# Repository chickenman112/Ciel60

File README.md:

# Ciel60
Resources for Ciel60

I am not responsible if these files do not work

HS pcb uses RMI's footprints

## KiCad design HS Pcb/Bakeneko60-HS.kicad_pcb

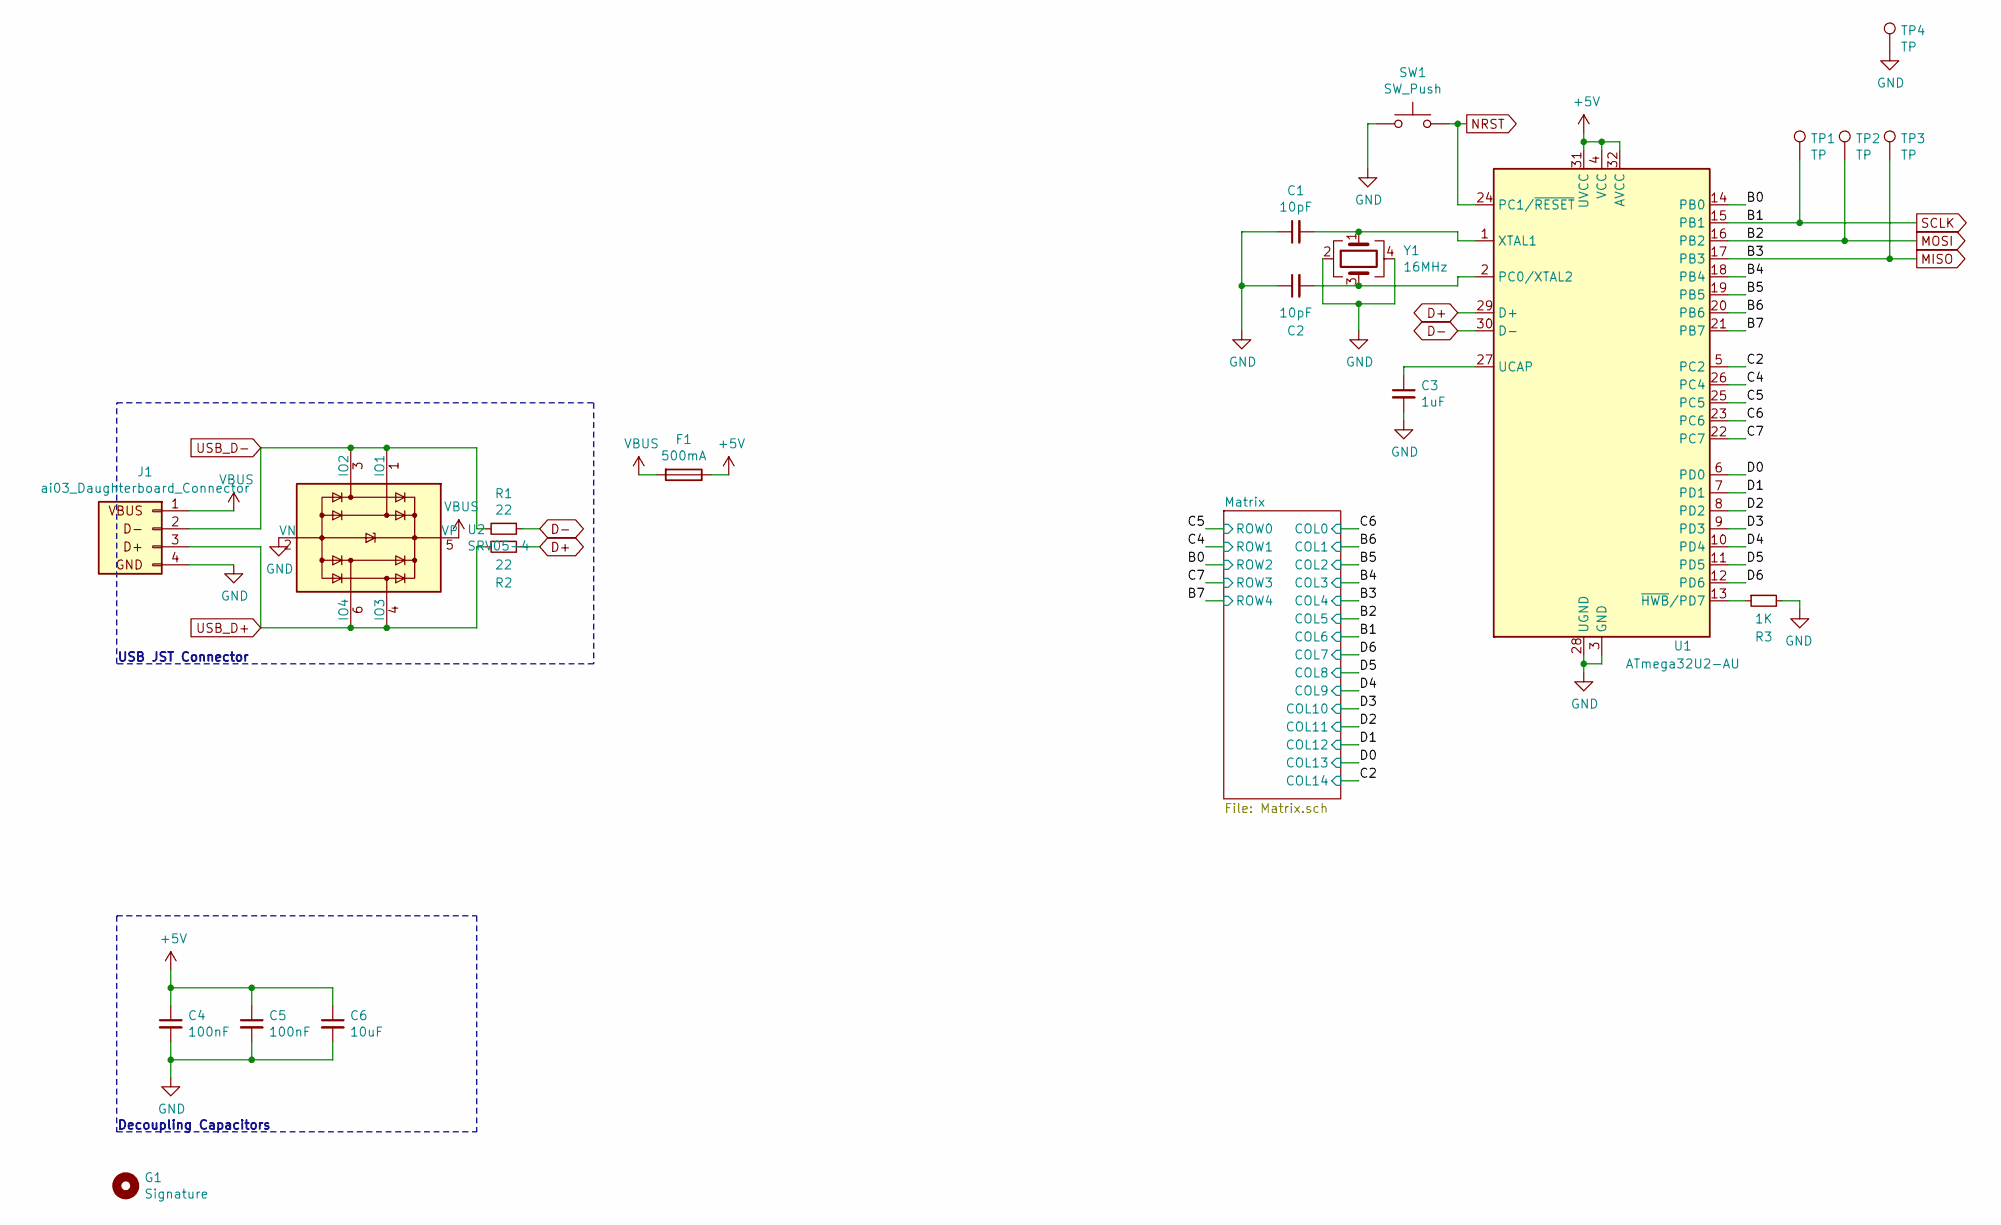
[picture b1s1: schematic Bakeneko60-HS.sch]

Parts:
C1, C2: 10pF; C_0603_1608Metric
C3: 1uF; C_0603_1608Metric
C4, C5: 100nF; C_0603_1608Metric
C6: 10uF; C_0805_2012Metric
F1: 500mA; Fuse_1206_3216Metric
G1: Signature
J1: ai03_Daughterboard_Connector; JST_SH_SM04B-SRSS-TB_1x04-1MP_P1.00mm_Horizontal
R1, R2: 22; R_0603_1608Metric
R3: 1K; R_0603_1608Metric
SW1: SW_Push; SW_SPST_TL3342
TP1, TP2, TP3, TP4: TP; TestPoint_Pad_D1.0mm
U1: ATmega32U2-AU; TQFP-32_7x7mm_P0.8mm
U2: SRV05-4; SOT-23-6
Y1: 16MHz; Crystal_SMD_3225-4Pin_3.2x2.5mm

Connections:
+5V: C4.1, C5.1, C6.1, F1.1, U1.4 (VCC), U1.31 (UVCC), U1.32 (AVCC)
/B0: U1.14 (PB0); also elsewhere on the board
/B4: U1.18 (PB4); also elsewhere on the board
/B5: U1.19 (PB5); also elsewhere on the board
/B6: U1.20 (PB6); also elsewhere on the board
/B7: U1.21 (PB7); also elsewhere on the board
/C2: U1.5 (PC2); also elsewhere on the board
/C4: U1.26 (PC4); also elsewhere on the board
/C5: U1.25 (PC5); also elsewhere on the board
/C6: U1.23 (PC6); also elsewhere on the board
/C7: U1.22 (PC7); also elsewhere on the board
/D0: U1.6 (PD0); also elsewhere on the board
/D1: U1.7 (PD1); also elsewhere on the board
/D2: U1.8 (PD2); also elsewhere on the board
/D3: U1.9 (PD3); also elsewhere on the board
/D4: U1.10 (PD4); also elsewhere on the board
/D5: U1.11 (PD5); also elsewhere on the board
/D6: U1.12 (PD6); also elsewhere on the board
D+: R2.2, U1.29 (D+)
D-: R1.1, U1.30 (D-)
GND: C1.1, C2.1, C3.2, C4.2, C5.2, C6.2, J1.4 (GND), R3.2, SW1.1, TP4.1, U1.3 (GND), U1.28 (UGND), U2.2 (VN), Y1.2, Y1.4
MISO: TP3.1, U1.17 (PB3); also elsewhere on the board
MOSI: TP2.1, U1.16 (PB2); also elsewhere on the board
NRST: SW1.2, U1.24 (PC1/~RESET)
unnamed: C1.2, U1.1 (XTAL1), Y1.1
unnamed: C2.2, U1.2 (PC0/XTAL2), Y1.3
unnamed: C3.1, U1.27 (UCAP)
unnamed: R3.1, U1.13 (~HWB~/PD7)
SCLK: TP1.1, U1.15 (PB1); also elsewhere on the board
USB_D+: J1.3 (D+), R2.1, U2.4 (IO3), U2.6 (IO4)
USB_D-: J1.2 (D-), R1.2, U2.1 (IO1), U2.3 (IO2)
VBUS: F1.2, J1.1 (VBUS), U2.5 (VP)

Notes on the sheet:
Decoupling Capacitors
USB JST Connector

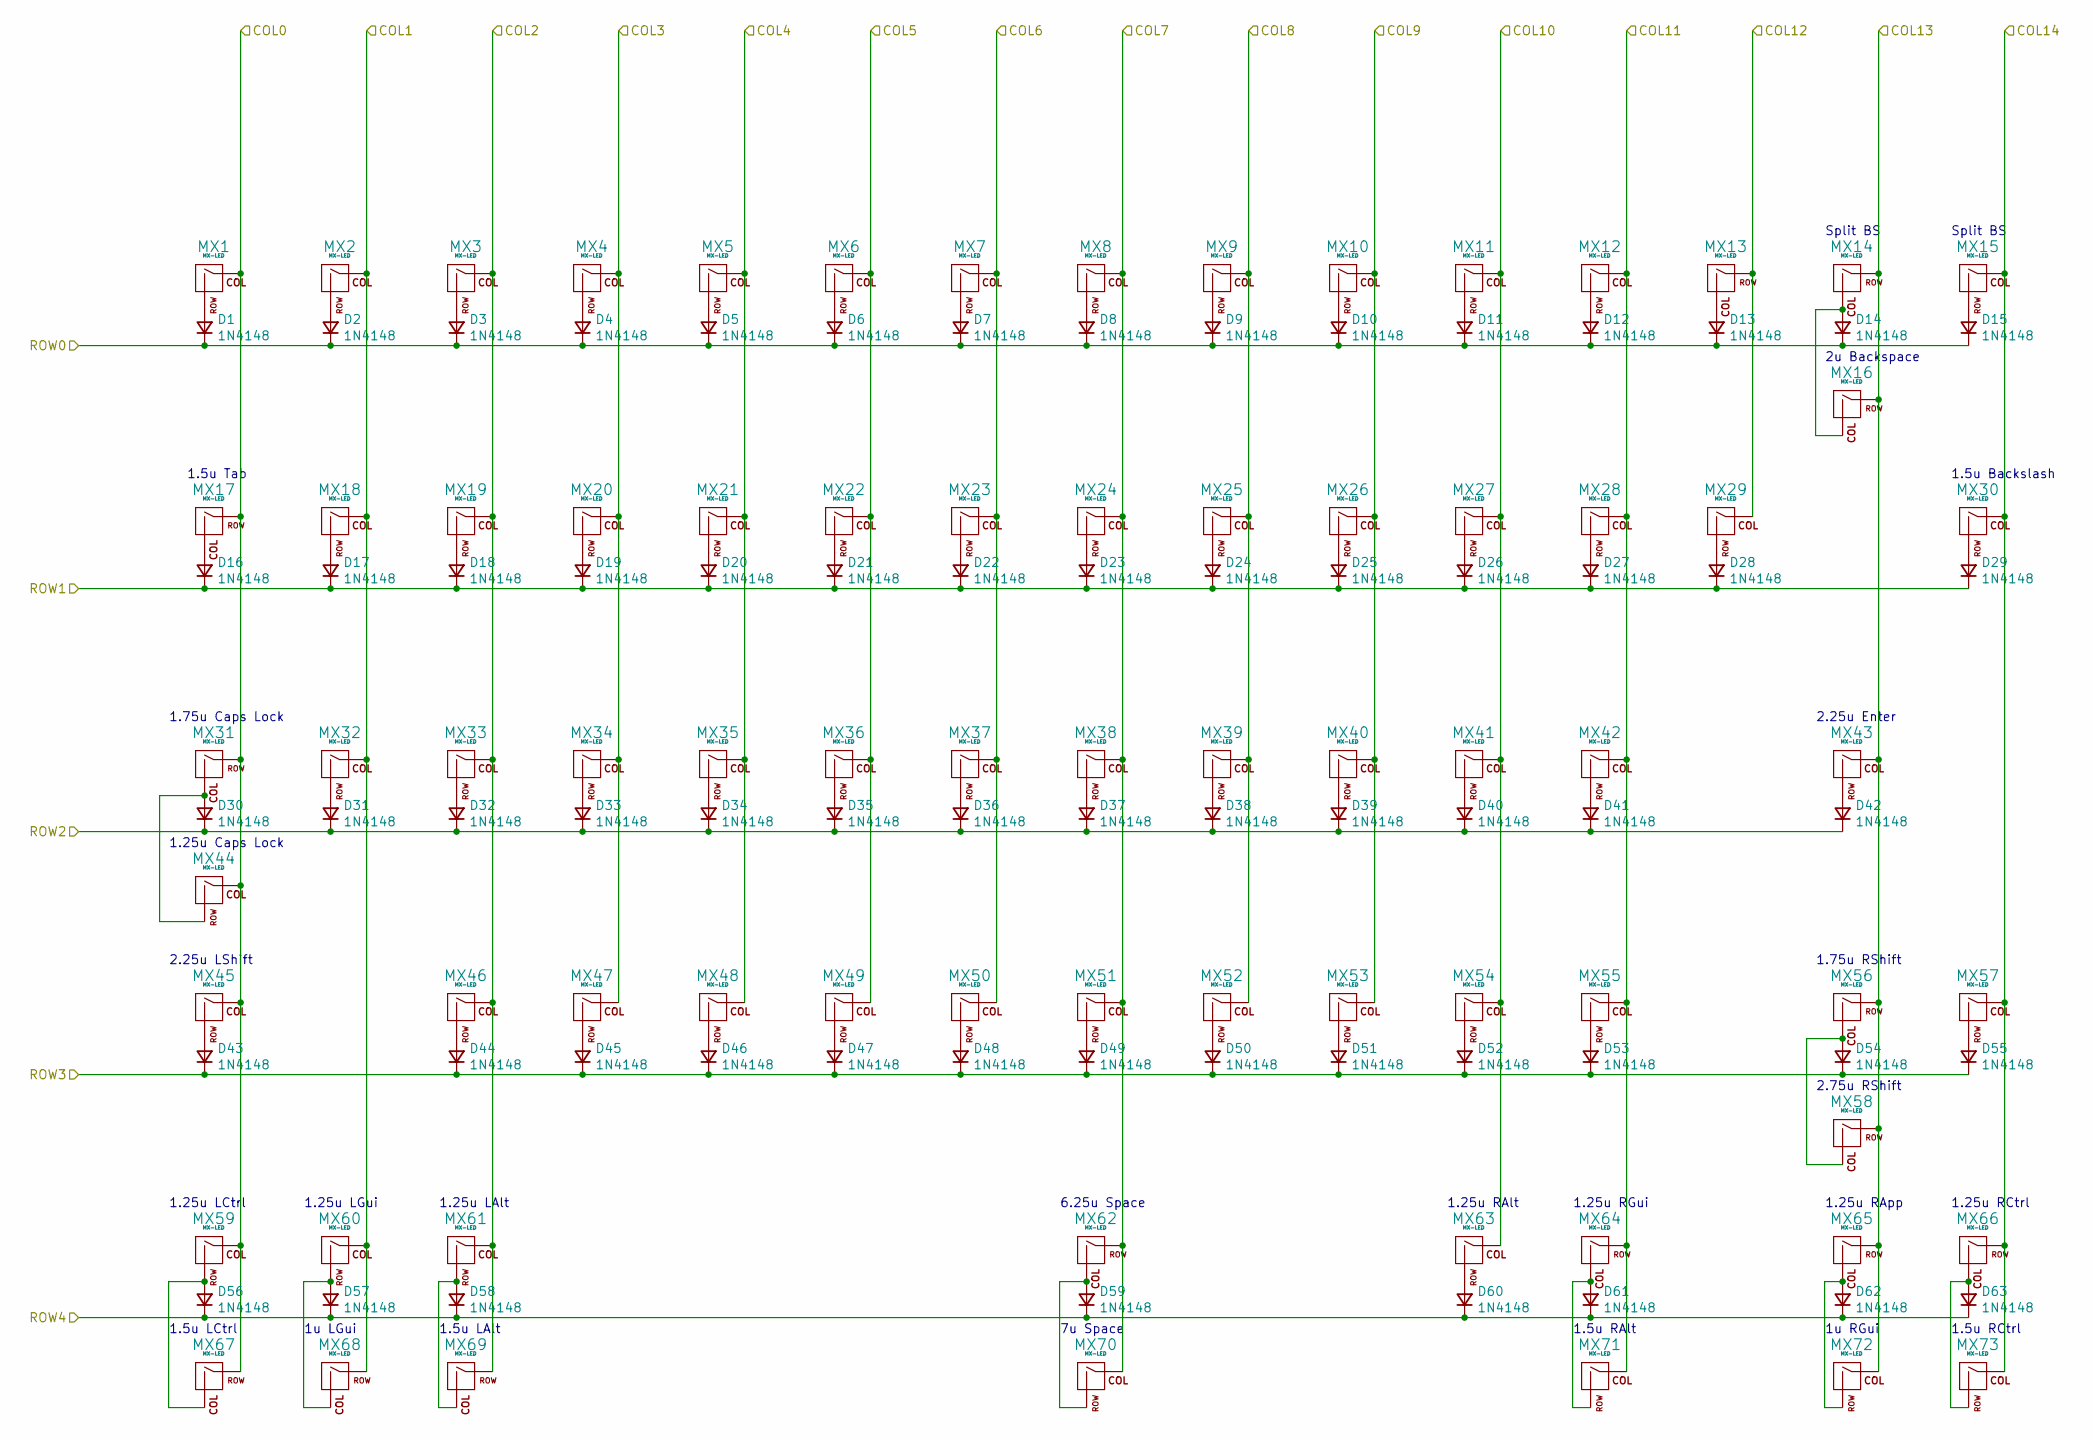
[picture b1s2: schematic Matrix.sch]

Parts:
D1, D2, D3, D4, D5, D6, D7, D8, D9, D10, D11, D12, D13, D14, D15, D16, D17, D18, D19, D20, D21, D22, D23, D24, D25, D26, D27, D28, D29, D30, D31, D32, D33, D34, D35, D36, D37, D38, D39, D40, D41, D42, D43, D44, D45, D46, D47, D48, D49, D50, D51, D52, D53, D54, D55, D56, D57, D58, D59, D60, D61, D62, D63: 1N4148; D_SOD-123-Pretty
MX1, MX2, MX3, MX4, MX5, MX6, MX7, MX8, MX9, MX10, MX11, MX12, MX13, MX14, MX15, MX18, MX19, MX20, MX21, MX22, MX23, MX24, MX25, MX26, MX27, MX28, MX29, MX32, MX33, MX34, MX35, MX36, MX37, MX38, MX39, MX40, MX41, MX42, MX46, MX47, MX48, MX49, MX50, MX51, MX52, MX53, MX54, MX55, MX57, MX68, MX72: MX-LED; MXOnly-1U-Hotswap
MX16: MX-LED; MXOnly-2U-Hotswap
MX17, MX30, MX67, MX69, MX71, MX73: MX-LED; MXOnly-1.5U-Hotswap
MX31, MX56: MX-LED; MXOnly-1.75U-Hotswap
MX43: MX-LED; MXOnly-2.25U-Hotswap-ReversedStabilizers
MX44, MX59, MX60, MX61, MX63, MX64, MX65, MX66: MX-LED; MXOnly-1.25U-Hotswap
MX45: MX-LED; MXOnly-2.25U-Hotswap
MX58: MX-LED; MXOnly-2.75U-Hotswap
MX62: MX-LED; MXOnly-6.25U-Hotswap-ReversedStabilizers
MX70: MX-LED; MXOnly-7U-Hotswap

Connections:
/B0: D30.1 (K), D31.1 (K), D32.1 (K), D33.1 (K), D34.1 (K), D35.1 (K), D36.1 (K), D37.1 (K), D38.1 (K), D39.1 (K), D40.1 (K), D41.1 (K), D42.1 (K); also elsewhere on the board
/B4: MX4.1 (COL), MX20.1 (COL), MX34.1 (COL), MX47.1 (COL); also elsewhere on the board
/B5: MX3.1 (COL), MX19.1 (COL), MX33.1 (COL), MX46.1 (COL), MX61.1 (COL), MX69.2 (ROW); also elsewhere on the board
/B6: MX2.1 (COL), MX18.1 (COL), MX32.1 (COL), MX60.1 (COL), MX68.2 (ROW); also elsewhere on the board
/B7: D56.1 (K), D57.1 (K), D58.1 (K), D59.1 (K), D60.1 (K), D61.1 (K), D62.1 (K), D63.1 (K); also elsewhere on the board
/C2: MX15.1 (COL), MX30.1 (COL), MX57.1 (COL), MX66.2 (ROW), MX73.1 (COL); also elsewhere on the board
/C4: D16.1 (K), D17.1 (K), D18.1 (K), D19.1 (K), D20.1 (K), D21.1 (K), D22.1 (K), D23.1 (K), D24.1 (K), D25.1 (K), D26.1 (K), D27.1 (K), D28.1 (K), D29.1 (K); also elsewhere on the board
/C5: D1.1 (K), D2.1 (K), D3.1 (K), D4.1 (K), D5.1 (K), D6.1 (K), D7.1 (K), D8.1 (K), D9.1 (K), D10.1 (K), D11.1 (K), D12.1 (K), D13.1 (K), D14.1 (K), D15.1 (K); also elsewhere on the board
/C6: MX1.1 (COL), MX17.2 (ROW), MX31.2 (ROW), MX44.1 (COL), MX45.1 (COL), MX59.1 (COL), MX67.2 (ROW); also elsewhere on the board
/C7: D43.1 (K), D44.1 (K), D45.1 (K), D46.1 (K), D47.1 (K), D48.1 (K), D49.1 (K), D50.1 (K), D51.1 (K), D52.1 (K), D53.1 (K), D54.1 (K), D55.1 (K); also elsewhere on the board
/D0: MX14.2 (ROW), MX16.2 (ROW), MX43.1 (COL), MX56.2 (ROW), MX58.2 (ROW), MX65.2 (ROW), MX72.1 (COL); also elsewhere on the board
/D1: MX13.2 (ROW), MX29.1 (COL); also elsewhere on the board
/D2: MX12.1 (COL), MX28.1 (COL), MX42.1 (COL), MX55.1 (COL), MX64.2 (ROW), MX71.1 (COL); also elsewhere on the board
/D3: MX11.1 (COL), MX27.1 (COL), MX41.1 (COL), MX54.1 (COL), MX63.1 (COL); also elsewhere on the board
/D4: MX10.1 (COL), MX26.1 (COL), MX40.1 (COL), MX53.1 (COL); also elsewhere on the board
/D5: MX9.1 (COL), MX25.1 (COL), MX39.1 (COL), MX52.1 (COL); also elsewhere on the board
/D6: MX8.1 (COL), MX24.1 (COL), MX38.1 (COL), MX51.1 (COL), MX62.2 (ROW), MX70.1 (COL); also elsewhere on the board
MISO: MX5.1 (COL), MX21.1 (COL), MX35.1 (COL), MX48.1 (COL); also elsewhere on the board
MOSI: MX6.1 (COL), MX22.1 (COL), MX36.1 (COL), MX49.1 (COL); also elsewhere on the board
unnamed: D1.2 (A), MX1.2 (ROW)
unnamed: D2.2 (A), MX2.2 (ROW)
unnamed: D3.2 (A), MX3.2 (ROW)
unnamed: D4.2 (A), MX4.2 (ROW)
unnamed: D5.2 (A), MX5.2 (ROW)
unnamed: D6.2 (A), MX6.2 (ROW)
unnamed: D7.2 (A), MX7.2 (ROW)
unnamed: D8.2 (A), MX8.2 (ROW)
unnamed: D9.2 (A), MX9.2 (ROW)
unnamed: D10.2 (A), MX10.2 (ROW)
unnamed: D11.2 (A), MX11.2 (ROW)
unnamed: D12.2 (A), MX12.2 (ROW)
unnamed: D13.2 (A), MX13.1 (COL)
unnamed: D14.2 (A), MX14.1 (COL), MX16.1 (COL)
unnamed: D15.2 (A), MX15.2 (ROW)
unnamed: D16.2 (A), MX17.1 (COL)
unnamed: D17.2 (A), MX18.2 (ROW)
unnamed: D18.2 (A), MX19.2 (ROW)
unnamed: D19.2 (A), MX20.2 (ROW)
unnamed: D20.2 (A), MX21.2 (ROW)
unnamed: D21.2 (A), MX22.2 (ROW)
unnamed: D22.2 (A), MX23.2 (ROW)
unnamed: D23.2 (A), MX24.2 (ROW)
unnamed: D24.2 (A), MX25.2 (ROW)
unnamed: D25.2 (A), MX26.2 (ROW)
unnamed: D26.2 (A), MX27.2 (ROW)
unnamed: D27.2 (A), MX28.2 (ROW)
unnamed: D28.2 (A), MX29.2 (ROW)
unnamed: D29.2 (A), MX30.2 (ROW)
unnamed: D30.2 (A), MX31.1 (COL), MX44.2 (ROW)
unnamed: D31.2 (A), MX32.2 (ROW)
unnamed: D32.2 (A), MX33.2 (ROW)
unnamed: D33.2 (A), MX34.2 (ROW)
unnamed: D34.2 (A), MX35.2 (ROW)
unnamed: D35.2 (A), MX36.2 (ROW)
unnamed: D36.2 (A), MX37.2 (ROW)
unnamed: D37.2 (A), MX38.2 (ROW)
unnamed: D38.2 (A), MX39.2 (ROW)
unnamed: D39.2 (A), MX40.2 (ROW)
unnamed: D40.2 (A), MX41.2 (ROW)
unnamed: D41.2 (A), MX42.2 (ROW)
unnamed: D42.2 (A), MX43.2 (ROW)
unnamed: D43.2 (A), MX45.2 (ROW)
unnamed: D44.2 (A), MX46.2 (ROW)
unnamed: D45.2 (A), MX47.2 (ROW)
unnamed: D46.2 (A), MX48.2 (ROW)
unnamed: D47.2 (A), MX49.2 (ROW)
unnamed: D48.2 (A), MX50.2 (ROW)
unnamed: D49.2 (A), MX51.2 (ROW)
unnamed: D50.2 (A), MX52.2 (ROW)
unnamed: D51.2 (A), MX53.2 (ROW)
unnamed: D52.2 (A), MX54.2 (ROW)
unnamed: D53.2 (A), MX55.2 (ROW)
unnamed: D54.2 (A), MX56.1 (COL), MX58.1 (COL)
unnamed: D55.2 (A), MX57.2 (ROW)
unnamed: D56.2 (A), MX59.2 (ROW), MX67.1 (COL)
unnamed: D57.2 (A), MX60.2 (ROW), MX68.1 (COL)
unnamed: D58.2 (A), MX61.2 (ROW), MX69.1 (COL)
unnamed: D59.2 (A), MX62.1 (COL), MX70.2 (ROW)
unnamed: D60.2 (A), MX63.2 (ROW)
unnamed: D61.2 (A), MX64.1 (COL), MX71.2 (ROW)
unnamed: D62.2 (A), MX65.1 (COL), MX72.2 (ROW)
unnamed: D63.2 (A), MX66.1 (COL), MX73.2 (ROW)
SCLK: MX7.1 (COL), MX23.1 (COL), MX37.1 (COL), MX50.1 (COL); also elsewhere on the board

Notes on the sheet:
1.5u Tab
1.75u Caps Lock
2.25u Enter
1.25u Caps Lock
2.25u LShift
1.25u LCtrl
1.25u LGui
1.25u LAlt
1.5u LCtrl
1u LGui
1.5u LAlt
7u Space
6.25u Space
1.5u RCtrl
1u RGui
1.5u RAlt
1.25u RAlt
1.25u RGui
1.25u RApp
1.25u RCtrl
2.75u RShift
1.75u RShift
1.5u Backslash
2u Backspace
Split BS

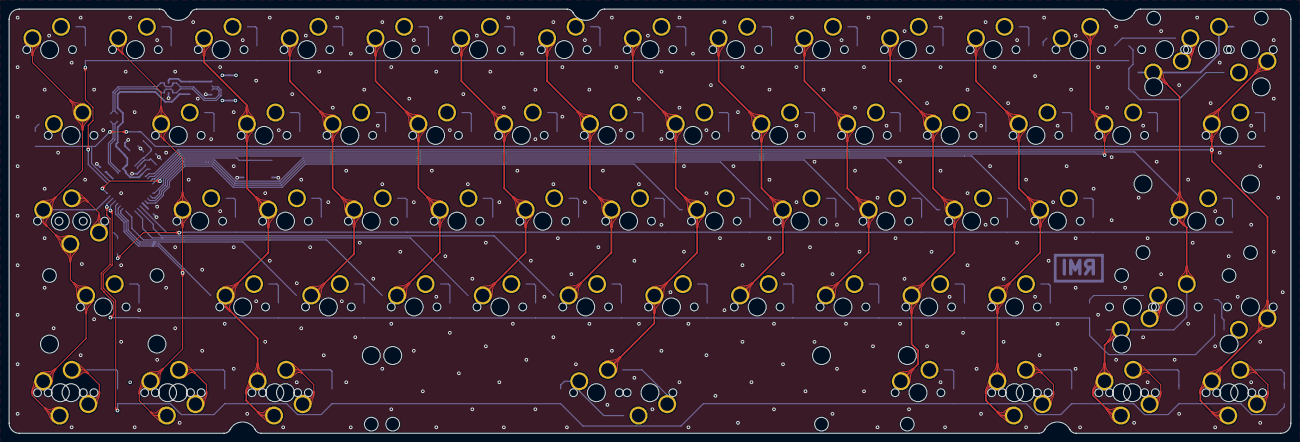
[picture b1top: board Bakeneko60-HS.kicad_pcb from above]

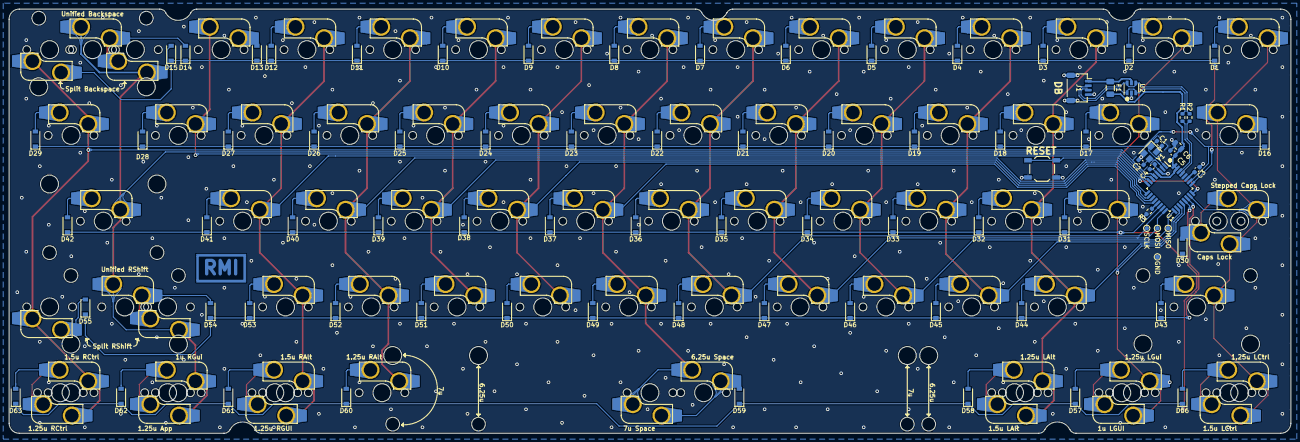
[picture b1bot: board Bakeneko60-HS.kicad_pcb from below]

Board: 2 copper layers, 284.7 x 94.2 mm, 156 parts (156 on the bottom side), 95 nets.

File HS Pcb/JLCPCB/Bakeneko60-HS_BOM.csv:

Comment,Designator,Footprint,LCSC
10pF,"C2,C1",Capacitor_SMD:C_0603_1608Metric,
1uF,C3,Capacitor_SMD:C_0603_1608Metric,
100nF,"C4,C5",Capacitor_SMD:C_0603_1608Metric,
10uF,C6,Capacitor_SMD:C_0805_2012Metric,
1N4148,"D1,D2,D3,D4,D5,D6,D7,D8,D9,D10,D11,D12,D13,D14,D16,D17,D18,D19,D20,D21,D22,D23,D24,D25,D26,D27,D28,D30,D31,D32,D33,D34,D35,D36,D37,D38,D39,D40,D41,D42,D43,D44,D45,D46,D47,D48,D49,D50,D51,D52,D53,D56,D57,D58,D59,D63,D62,D61,D60,D15,D55,D54,D29",random-keyboard-parts:D_SOD-123-Pretty,
500mA,F1,Fuse:Fuse_1206_3216Metric,
Conn_01x04,J1,Connector_JST:JST_SH_SM04B-SRSS-TB_1x04-1MP_P1.00mm_Horizontal,
MX-LED,"MX1,MX2,MX3,MX4,MX5,MX6,MX7,MX8,MX9,MX10,MX11,MX12,MX13,MX18,MX19,MX20,MX21,MX22,MX23,MX24,MX25,MX26,MX27,MX28,MX29,MX32,MX33,MX34,MX35,MX36,MX37,MX38,MX39,MX40,MX41,MX42,MX46,MX47,MX48,MX49,MX50,MX51,MX52,MX53,MX54,MX55,MX68,MX72,MX57,MX15,MX14",MX_HS:MXOnly-1U-Hotswap,
MX-LED,MX16,MX_HS:MXOnly-2U-Hotswap,
MX-LED,"MX17,MX67,MX69,MX73,MX71,MX30",MX_HS:MXOnly-1.5U-Hotswap,
MX-LED,"MX31,MX56",MX_HS:MXOnly-1.75U-Hotswap,
MX-LED,MX43,MX_HS:MXOnly-2.25U-Hotswap-ReversedStabilizers,
MX-LED,MX45,MX_HS:MXOnly-2.25U-Hotswap,
MX-LED,MX58,MX_HS:MXOnly-2.75U-Hotswap,
MX-LED,"MX59,MX60,MX61,MX44,MX66,MX65,MX64,MX63",MX_HS:MXOnly-1.25U-Hotswap,
MX-LED,MX62,MX_HS:MXOnly-6.25U-Hotswap-ReversedStabilizers,
MX-LED,MX70,MX_HS:MXOnly-7U-Hotswap,
22,"R1,R2",Resistor_SMD:R_0603_1608Metric,
1K,R3,Resistor_SMD:R_0603_1608Metric,
SW_Push,SW1,Button_Switch_SMD:SW_SPST_TL3342,
TP,"TP1,TP2,TP3,TP4",TestPoint:TestPoint_Pad_D1.0mm,
ATmega32U2-AU,U1,Package_QFP:TQFP-32_7x7mm_P0.8mm,
SRV05-4,U2,Package_TO_SOT_SMD:SOT-23-6,
16MHz,Y1,Crystal:Crystal_SMD_3225-4Pin_3.2x2.5mm,
